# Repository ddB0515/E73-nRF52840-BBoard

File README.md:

nRF52840-BBoard

Based on Ebyte E73 module with nRF52840
More details here: https://www.ebyte.com/en/product-view-news.aspx?id=445

Managed to fit all into breakout board (4 layers) with Lipo charger (not yet tested fully) and USB-C with modified Adafruit nRF52 Bootloader
https://github.com/ddB0515/Adafruit_nRF52_Bootloader/tree/nrf52840-bboard

when managed to build and get bootloader you need to flash it (I have JLink so was easy to get it flashed)
Double click on reset button to get into DFU mode

Bootloader is in `bootloader` folder and should work if you don't wanna build it

To flash it with JLink all you need is in `bootloader` folder:
nrf52840_bboard_bootloader-0.5.1-2-g881dac1-dirty_s140_6.1.1.hex

To update it via serial(if already flashed via Jlink)

`
adafruit-nrfutil --verbose dfu serial --package nrf52840_bboard_bootloader-0.5.1-2-g881dac1-dirty_s140_6.1.1.zip --port /dev/ttyACM0 -b 115200 --singlebank --touch 1200
`

# Interactive BOM
[Interactive BOM](http://htmlpreview.github.io/?https://raw.githubusercontent.com/ddB0515/nRF52840-BBoard/main/bom/ibom.html)

# TODO
- Submit board to Adafruit Bootloader repo
- Add board to Communitiy nRF52 (https://github.com/jpconstantineau/Community_nRF52_Arduino)
- Get more samples/demos to provide with board

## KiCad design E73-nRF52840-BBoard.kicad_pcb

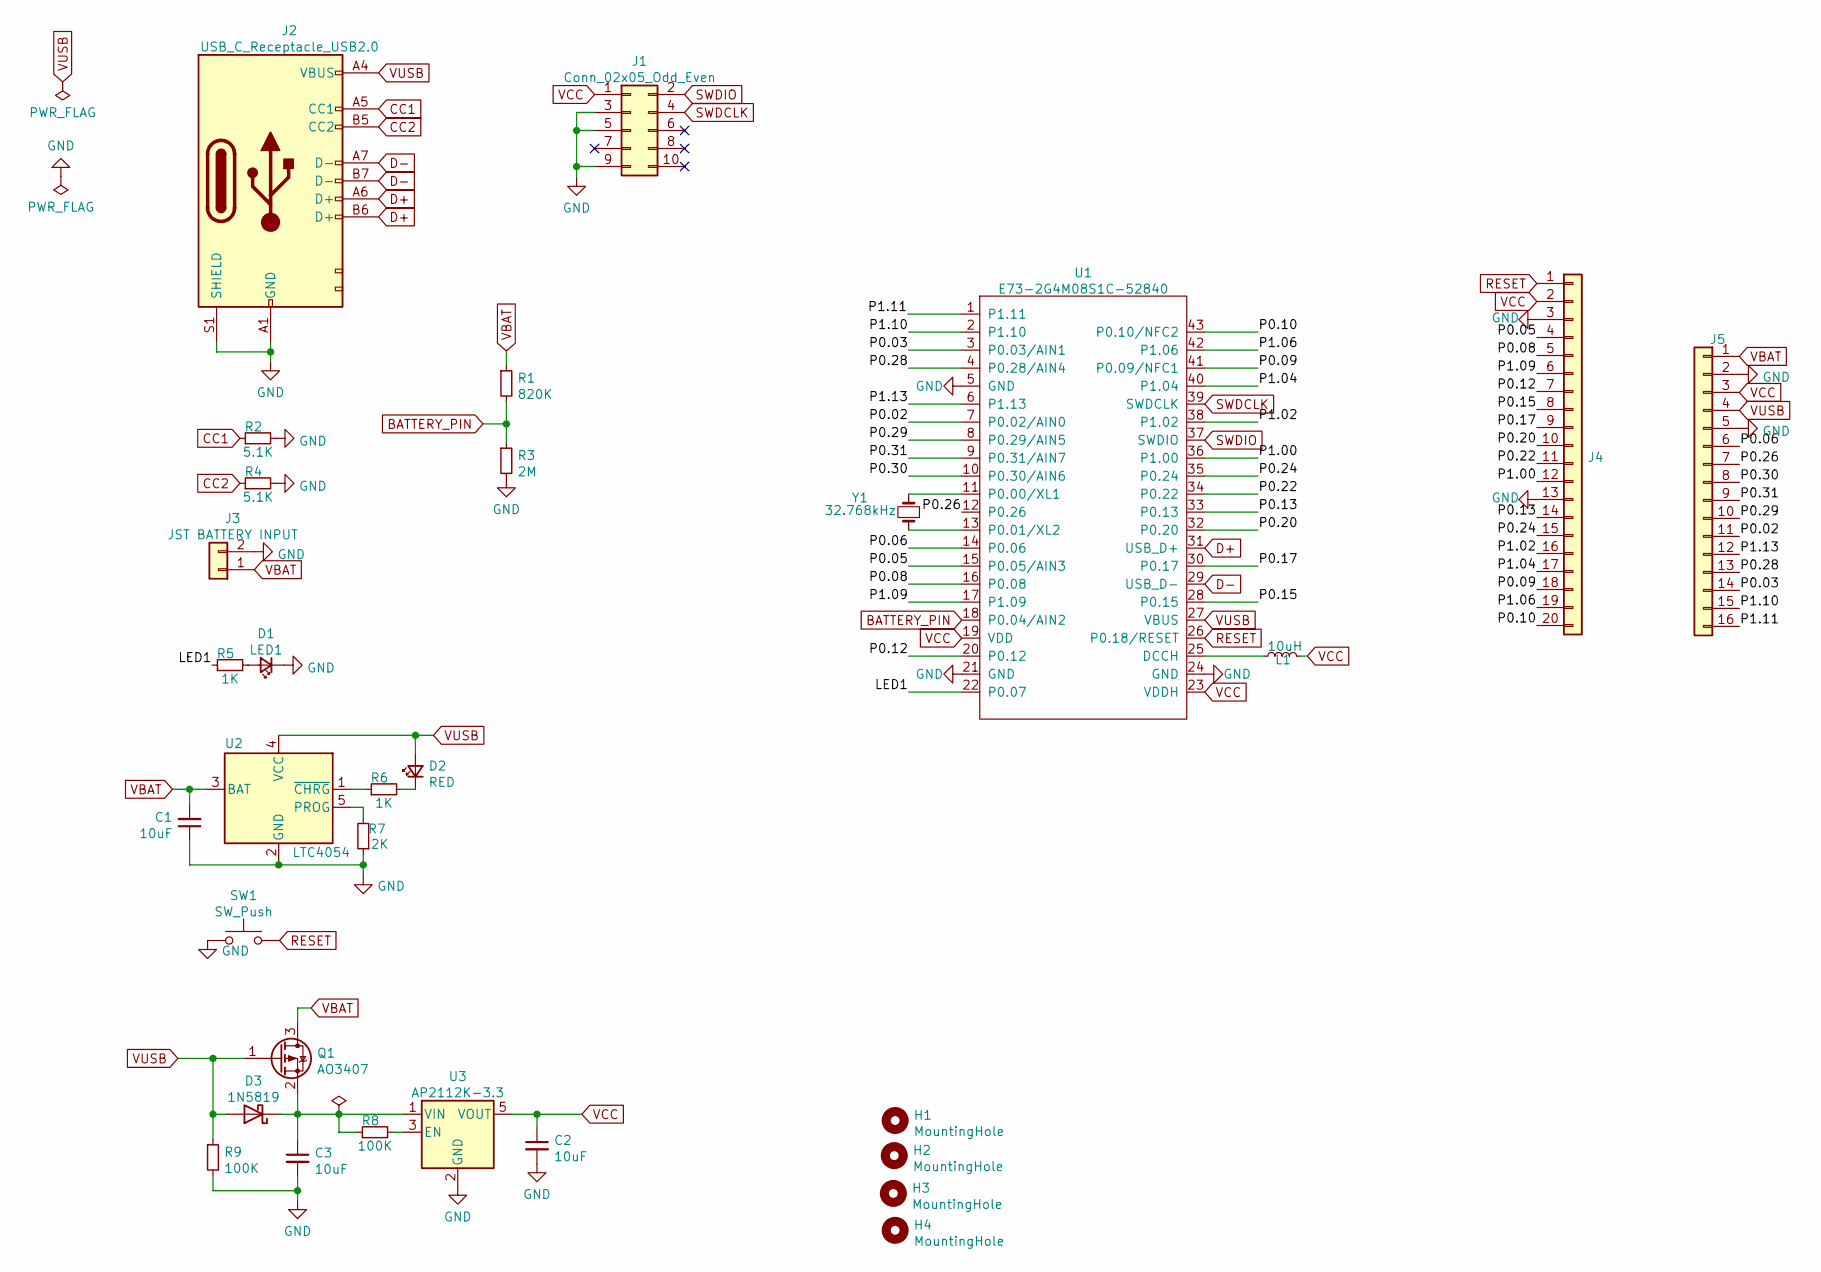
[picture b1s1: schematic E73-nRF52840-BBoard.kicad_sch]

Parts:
C1, C2, C3: 10uF; C_0402_1005Metric_Pad0.74x0.62mm_HandSolder
D1: LED1; LED_0603_1608Metric_Pad1.05x0.95mm_HandSolder
D2: RED; LED_0603_1608Metric_Pad1.05x0.95mm_HandSolder
D3: 1N5819; D_SOD-323_HandSoldering
H1, H2, H3, H4: MountingHole; MountingHole_2mm
J1: Conn_02x05_Odd_Even; PinHeader_2x05_P1.27mm_Vertical_SMD
J2: USB_C_Receptacle_USB2.0; USB-C_C168688
J3: JST BATTERY INPUT; JST_GH_SM02B-GHS-TB_1x02-1MP_P1.25mm_Horizontal
J4: Conn_01x20; PinHeader_1x20_P2.54mm_Vertical
J5: Conn_01x16; PinHeader_1x16_P2.54mm_Vertical
L1: 10uH; L_0603_1608Metric_Pad1.05x0.95mm_HandSolder
Q1: AO3407; SOT-23
R1: 820K; R_0603_1608Metric
R2, R4: 5.1K; R_0603_1608Metric
R3: 2M; R_0603_1608Metric
R5, R6: 1K; R_0603_1608Metric
R7: 2K; R_0603_1608Metric
R8, R9: 100K; R_0603_1608Metric
SW1: SW_Push; KMR621NG
U1: E73-2G4M08S1C-52840
U2: LTC4054; TSOT-23-5
U3: AP2112K-3.3; SOT-23-5
Y1: 32.768kHz; Crystal_SMD_2012-2Pin_2.0x1.2mm

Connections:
/LED1: R5.1, U1.22 (P0.07)
/P0.02: J5.11, U1.7 (P0.02/AIN0)
/P0.03: J5.14, U1.3 (P0.03/AIN1)
/P0.05: J4.4, U1.15 (P0.05/AIN3)
/P0.06: J5.6, U1.14 (P0.06)
/P0.08: J4.5, U1.16 (P0.08)
/P0.09: J4.18, U1.41 (P0.09/NFC1)
/P0.10: J4.20, U1.43 (P0.10/NFC2)
/P0.12: J4.7, U1.20 (P0.12)
/P0.13: J4.14, U1.33 (P0.13)
/P0.15: J4.8, U1.28 (P0.15)
/P0.17: J4.9, U1.30 (P0.17)
/P0.20: J4.10, U1.32 (P0.20)
/P0.22: J4.11, U1.34 (P0.22)
/P0.24: J4.15, U1.35 (P0.24)
/P0.26: J5.7, U1.12 (P0.26)
/P0.28: J5.13, U1.4 (P0.28/AIN4)
/P0.29: J5.10, U1.8 (P0.29/AIN5)
/P0.30: J5.8, U1.10 (P0.30/AIN6)
/P0.31: J5.9, U1.9 (P0.31/AIN7)
/P1.00: J4.12, U1.36 (P1.00)
/P1.02: J4.16, U1.38 (P1.02)
/P1.04: J4.17, U1.40 (P1.04)
/P1.06: J4.19, U1.42 (P1.06)
/P1.09: J4.6, U1.17 (P1.09)
/P1.10: J5.15, U1.2 (P1.10)
/P1.11: J5.16, U1.1 (P1.11)
/P1.13: J5.12, U1.6 (P1.13)
BATTERY_PIN: R1.2, R3.1, U1.18 (P0.04/AIN2)
CC1: J2.A5 (CC1), R2.1
CC2: J2.B5 (CC2), R4.1
D+: J2.A6 (D+), J2.B6 (D+), U1.31 (USB_D+)
D-: J2.A7 (D-), J2.B7 (D-), U1.29 (USB_D-)
GND: C1.1, C2.2, C3.2, D1.1 (K), J1.3, J1.5, J1.9, J2.A1 (GND), J2.S1 (SHIELD), J3.2, J4.3, J4.13, J5.2, J5.5, R2.2, R3.2, R4.2, R7.1, R9.2, SW1.1, U1.5 (GND), U1.21 (GND), U1.24 (GND), U2.2 (GND), U3.2 (GND)
unnamed: C3.1, D3.1 (K), Q1.2 (S), R8.1, U3.1 (VIN)
unnamed: D1.2 (A), R5.2
unnamed: D2.1 (K), R6.2
unnamed: L1.1, U1.25 (DCCH)
unnamed: R6.1, U2.1 (~CHRG)
unnamed: R7.2, U2.5 (PROG)
unnamed: R8.2, U3.3 (EN)
unnamed: U1.11 (P0.00/XL1), Y1.2
unnamed: U1.13 (P0.01/XL2), Y1.1
RESET: J4.1, SW1.2, U1.26 (P0.18/RESET)
SWDCLK: J1.4, U1.39 (SWDCLK)
SWDIO: J1.2, U1.37 (SWDIO)
VBAT: C1.2, J3.1, J5.1, Q1.3 (D), R1.1, U2.3 (BAT)
VCC: C2.1, J1.1, J4.2, J5.3, L1.2, U1.19 (VDD), U1.23 (VDDH), U3.5 (VOUT)
VUSB: D2.2 (A), D3.2 (A), J2.A4 (VBUS), J5.4, Q1.1 (G), R9.1, U1.27 (VBUS), U2.4 (VCC)

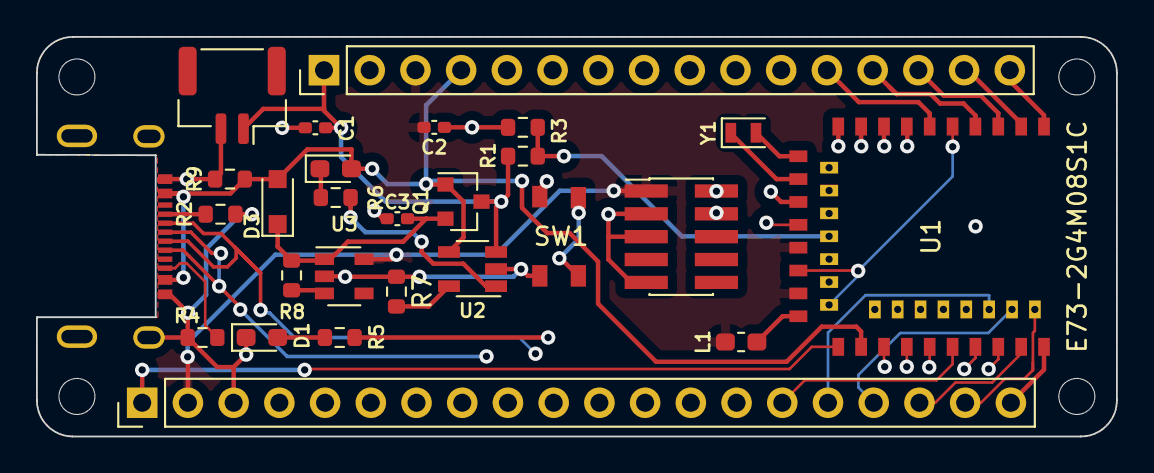
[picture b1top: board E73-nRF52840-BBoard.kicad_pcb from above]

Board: 4 copper layers, 60.0 x 22.2 mm, 31 parts (0 on the bottom side), 49 nets.

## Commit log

2021-05-14 initial rev1
2021-06-03 added final version after testing
2021-06-03 added images
2021-06-03 added bootloader
2021-06-04 added pdf schematic
2021-06-04 small changes to schematic
2021-06-04 added openmoko PID?VID in bootloader
2021-06-04 Update LICENSE
2021-06-04 updated licenses
2021-06-04 changed VID for bootloader
2021-06-09 updated files
